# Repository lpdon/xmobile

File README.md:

# X-Mobile #

### What is this repository for? ###

Repository for the development of the version 2015 of the X-Mobile robot.

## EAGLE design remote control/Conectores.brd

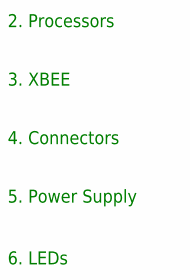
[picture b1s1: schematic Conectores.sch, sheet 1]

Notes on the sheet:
2. Processors
3. XBEE
4. Connectors
5. Power Supply
6. LEDs

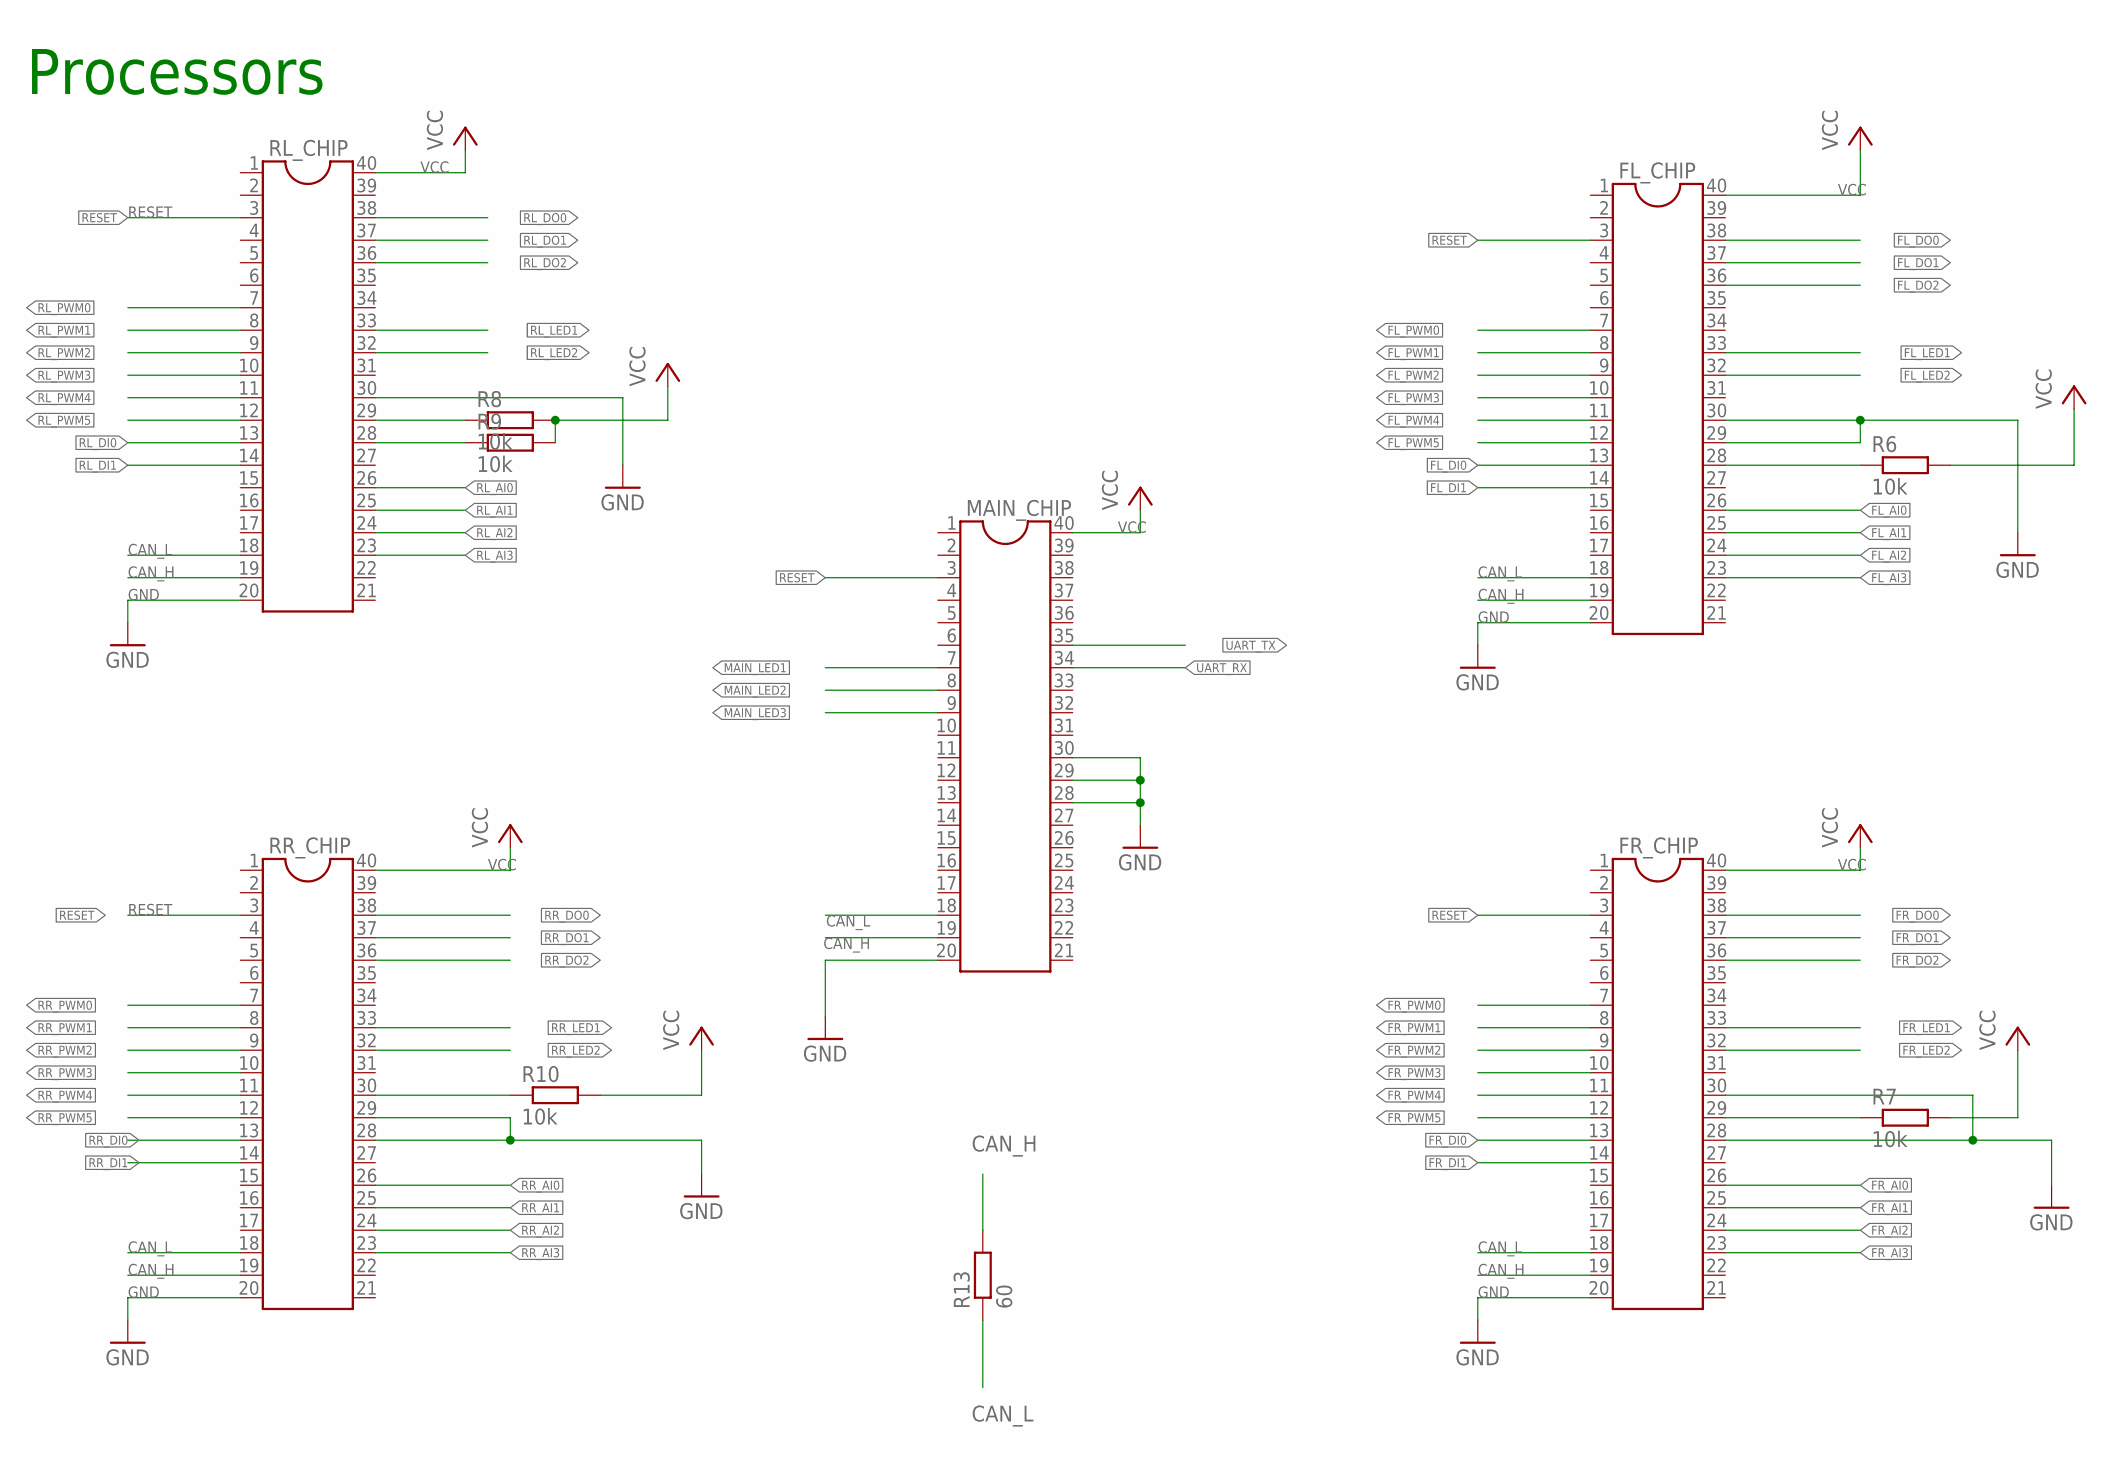
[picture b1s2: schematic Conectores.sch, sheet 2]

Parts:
FL_CHIP: DIL40
FR_CHIP: DIL40
MAIN_CHIP: DIL40
R6, R7, R8, R9, R10: 10k; M0805
R13: 60; R0805
RL_CHIP: DIL40
RR_CHIP: DIL40

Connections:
CAN_H: FL_CHIP.19, FR_CHIP.19, MAIN_CHIP.19, R13.2, RL_CHIP.19, RR_CHIP.19; also elsewhere on the board
CAN_L: FL_CHIP.18, FR_CHIP.18, MAIN_CHIP.18, R13.1, RL_CHIP.18, RR_CHIP.18; also elsewhere on the board
FL_AI0: FL_CHIP.26; also elsewhere on the board
FL_AI1: FL_CHIP.25; also elsewhere on the board
FL_AI2: FL_CHIP.24; also elsewhere on the board
FL_AI3: FL_CHIP.23; also elsewhere on the board
FL_DI0: FL_CHIP.13; also elsewhere on the board
FL_DI1: FL_CHIP.14; also elsewhere on the board
FL_DO0: FL_CHIP.38; also elsewhere on the board
FL_DO1: FL_CHIP.37; also elsewhere on the board
FL_DO2: FL_CHIP.36; also elsewhere on the board
FL_LED1: FL_CHIP.33; also elsewhere on the board
FL_LED2: FL_CHIP.32; also elsewhere on the board
FL_PWM0: FL_CHIP.7; also elsewhere on the board
FL_PWM1: FL_CHIP.8; also elsewhere on the board
FL_PWM2: FL_CHIP.9; also elsewhere on the board
FL_PWM3: FL_CHIP.10; also elsewhere on the board
FL_PWM4: FL_CHIP.11; also elsewhere on the board
FL_PWM5: FL_CHIP.12; also elsewhere on the board
FR_AI0: FR_CHIP.26; also elsewhere on the board
FR_AI1: FR_CHIP.25; also elsewhere on the board
FR_AI2: FR_CHIP.24; also elsewhere on the board
FR_AI3: FR_CHIP.23; also elsewhere on the board
FR_DI0: FR_CHIP.13; also elsewhere on the board
FR_DI1: FR_CHIP.14; also elsewhere on the board
FR_DIP2: FR_CHIP.29, R7.1
FR_DO0: FR_CHIP.38; also elsewhere on the board
FR_DO1: FR_CHIP.37; also elsewhere on the board
FR_DO2: FR_CHIP.36; also elsewhere on the board
FR_LED1: FR_CHIP.33; also elsewhere on the board
FR_LED2: FR_CHIP.32; also elsewhere on the board
FR_PWM0: FR_CHIP.7; also elsewhere on the board
FR_PWM1: FR_CHIP.8; also elsewhere on the board
FR_PWM2: FR_CHIP.9; also elsewhere on the board
FR_PWM3: FR_CHIP.10; also elsewhere on the board
FR_PWM4: FR_CHIP.11; also elsewhere on the board
FR_PWM5: FR_CHIP.12; also elsewhere on the board
GND: FL_CHIP.20, FL_CHIP.29, FL_CHIP.30, FR_CHIP.20, FR_CHIP.28, FR_CHIP.30, MAIN_CHIP.20, MAIN_CHIP.28, MAIN_CHIP.29, MAIN_CHIP.30, RL_CHIP.20, RL_CHIP.30, RR_CHIP.20, RR_CHIP.28, RR_CHIP.29; also elsewhere on the board
MAIN_LED1: MAIN_CHIP.7; also elsewhere on the board
MAIN_LED2: MAIN_CHIP.8; also elsewhere on the board
MAIN_LED3: MAIN_CHIP.9; also elsewhere on the board
unnamed: FL_CHIP.28, R6.1
RESET: FL_CHIP.3, FR_CHIP.3, MAIN_CHIP.3, RL_CHIP.3, RR_CHIP.3; also elsewhere on the board
RL_AI0: RL_CHIP.26; also elsewhere on the board
RL_AI1: RL_CHIP.25; also elsewhere on the board
RL_AI2: RL_CHIP.24; also elsewhere on the board
RL_AI3: RL_CHIP.23; also elsewhere on the board
RL_DI0: RL_CHIP.13; also elsewhere on the board
RL_DI1: RL_CHIP.14; also elsewhere on the board
RL_DIP2: R8.1, RL_CHIP.29
RL_DIP3: R9.1, RL_CHIP.28
RL_DO0: RL_CHIP.38; also elsewhere on the board
RL_DO1: RL_CHIP.37; also elsewhere on the board
RL_DO2: RL_CHIP.36; also elsewhere on the board
RL_LED1: RL_CHIP.33; also elsewhere on the board
RL_LED2: RL_CHIP.32; also elsewhere on the board
RL_PWM0: RL_CHIP.7; also elsewhere on the board
RL_PWM1: RL_CHIP.8; also elsewhere on the board
RL_PWM2: RL_CHIP.9; also elsewhere on the board
RL_PWM3: RL_CHIP.10; also elsewhere on the board
RL_PWM4: RL_CHIP.11; also elsewhere on the board
RL_PWM5: RL_CHIP.12; also elsewhere on the board
RR_AI0: RR_CHIP.26; also elsewhere on the board
RR_AI1: RR_CHIP.25; also elsewhere on the board
RR_AI2: RR_CHIP.24; also elsewhere on the board
RR_AI3: RR_CHIP.23; also elsewhere on the board
RR_DI0: RR_CHIP.13; also elsewhere on the board
RR_DI1: RR_CHIP.14; also elsewhere on the board
RR_DIP1: R10.1, RR_CHIP.30
RR_DO0: RR_CHIP.38; also elsewhere on the board
RR_DO1: RR_CHIP.37; also elsewhere on the board
RR_DO2: RR_CHIP.36; also elsewhere on the board
RR_LED1: RR_CHIP.33; also elsewhere on the board
RR_LED2: RR_CHIP.32; also elsewhere on the board
RR_PWM0: RR_CHIP.7; also elsewhere on the board
RR_PWM1: RR_CHIP.8; also elsewhere on the board
RR_PWM2: RR_CHIP.9; also elsewhere on the board
RR_PWM3: RR_CHIP.10; also elsewhere on the board
RR_PWM4: RR_CHIP.11; also elsewhere on the board
RR_PWM5: RR_CHIP.12; also elsewhere on the board
UART_RX: MAIN_CHIP.34; also elsewhere on the board
UART_TX: MAIN_CHIP.35; also elsewhere on the board
VCC: FL_CHIP.40, FR_CHIP.40, MAIN_CHIP.40, R6.2, R7.2, R8.2, R9.2, R10.2, RL_CHIP.40, RR_CHIP.40; also elsewhere on the board

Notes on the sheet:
Processors

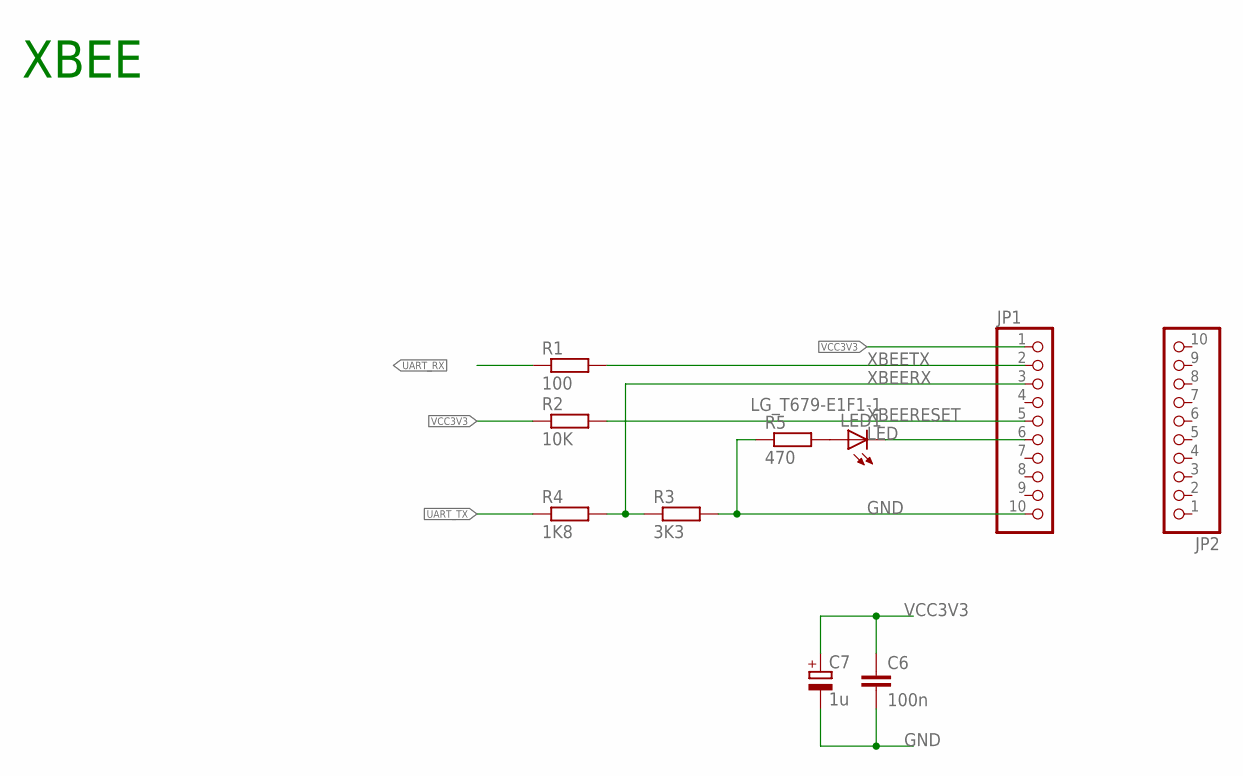
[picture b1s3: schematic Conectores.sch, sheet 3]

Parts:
C6: 100n; C0805
C7: 1u; CT3528
JP1, JP2: PINHD-1X10_2.00; 1X10M
LED1: LG_T679-E1F1-1; PLCC2
R1: 100; M0805
R2: 10K; M0805
R3: 3K3; M0805
R4: 1K8; M0805
R5: 470; M0805

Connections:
GND: C6.2, C7.-, JP1.10, R3.2, R5.1; also elsewhere on the board
LED: JP1.6, LED1.C
unnamed: LED1.A, R5.2
UART_RX: R1.1; also elsewhere on the board
UART_TX: R4.1; also elsewhere on the board
VCC3V3: C6.1, C7.+, JP1.1, R2.1; also elsewhere on the board
XBEERESET: JP1.5, R2.2
XBEERX: JP1.3, R3.1, R4.2
XBEETX: JP1.2, R1.2

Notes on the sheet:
XBEE

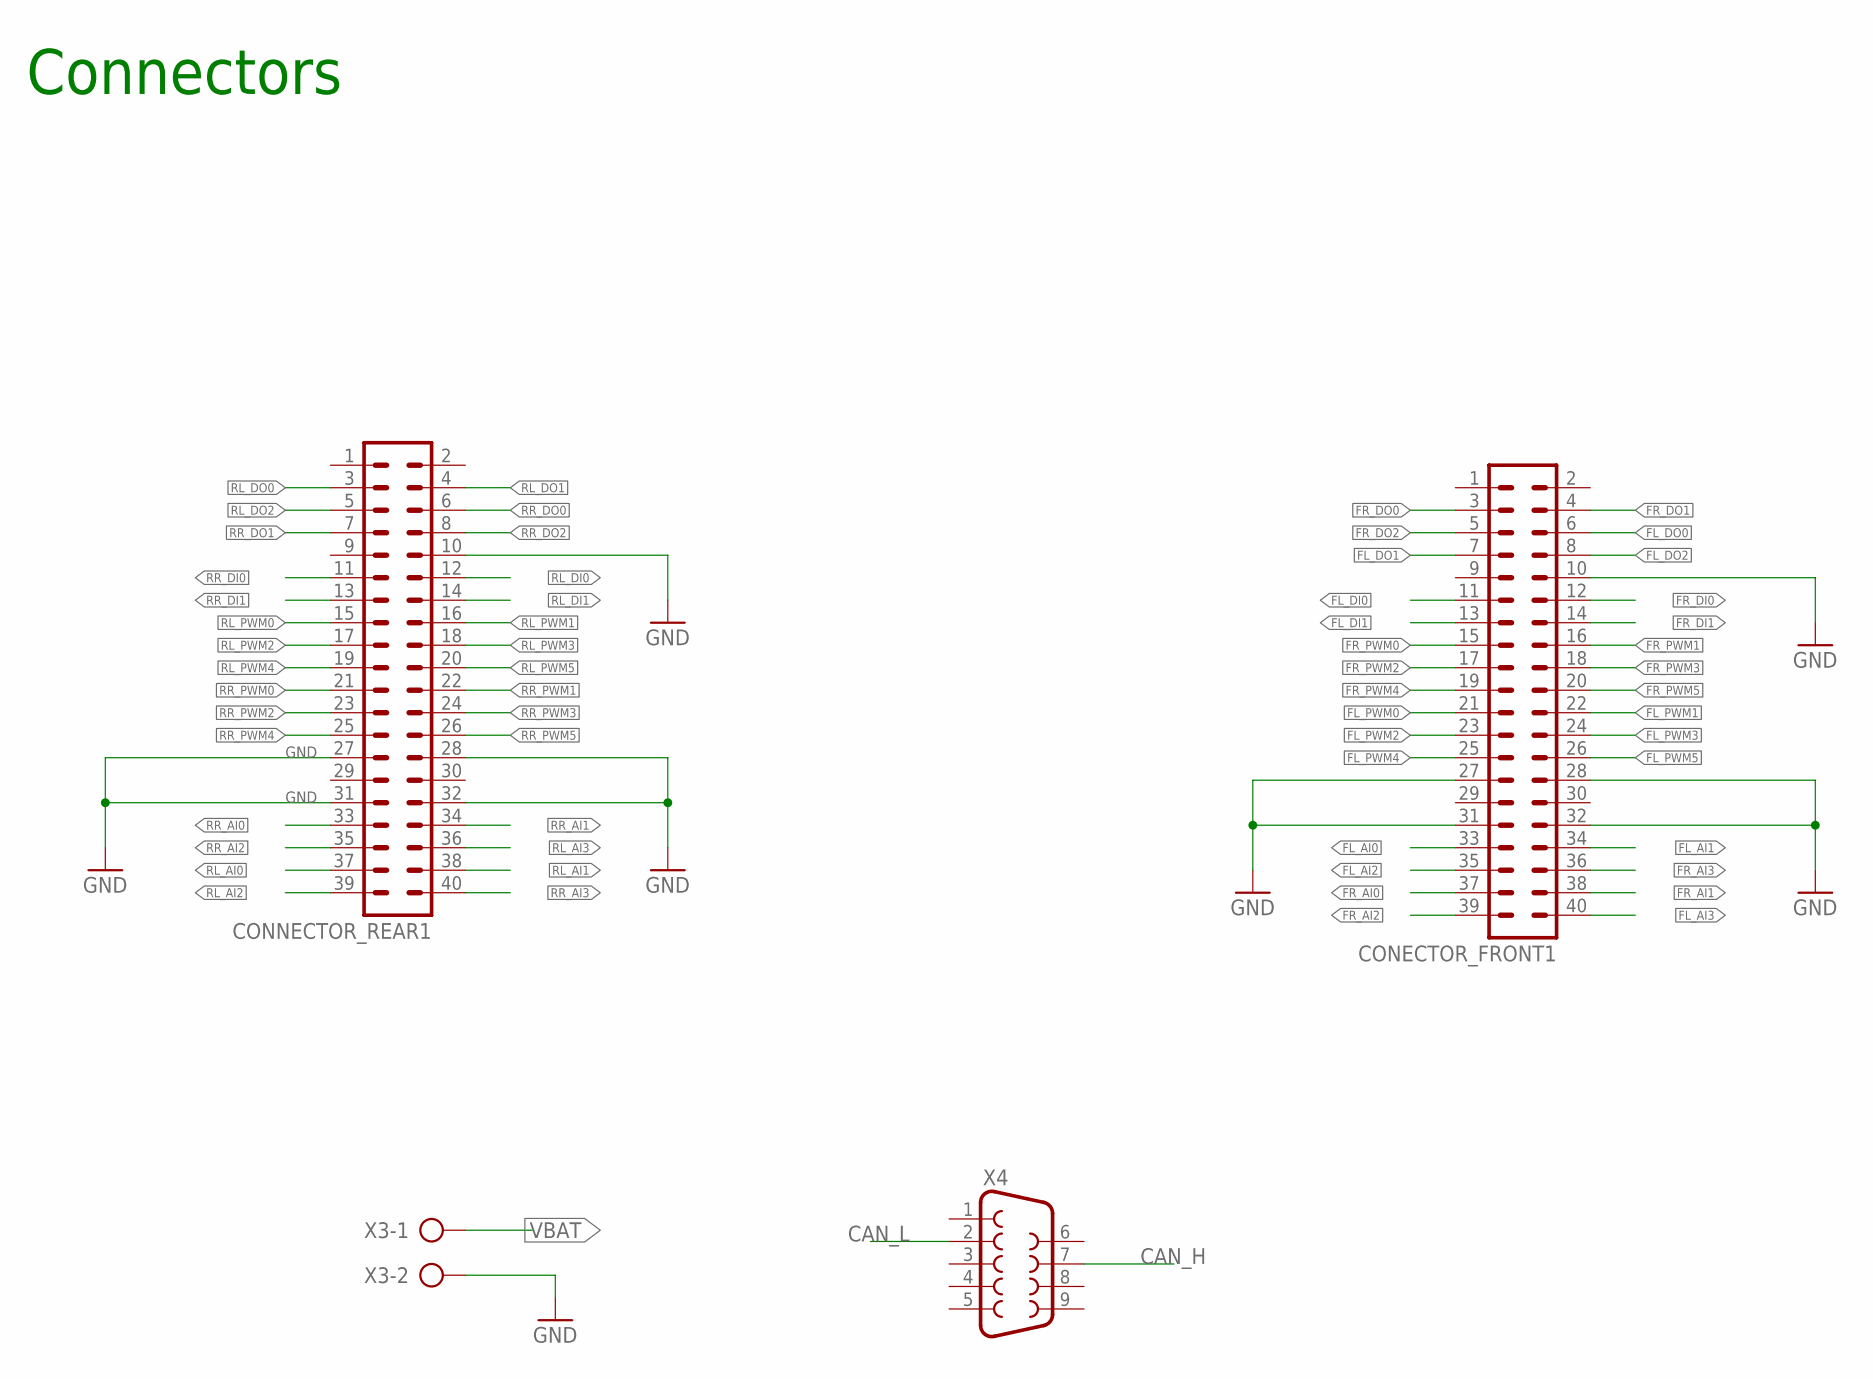
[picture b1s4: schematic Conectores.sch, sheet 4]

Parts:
CONECTOR_FRONT1: ML40
CONNECTOR_REAR1: ML40
X3: AK300/2
X4: F09HP

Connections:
CAN_H: X4.7; also elsewhere on the board
CAN_L: X4.2; also elsewhere on the board
FL_AI0: CONECTOR_FRONT1.33; also elsewhere on the board
FL_AI1: CONECTOR_FRONT1.34; also elsewhere on the board
FL_AI2: CONECTOR_FRONT1.35; also elsewhere on the board
FL_AI3: CONECTOR_FRONT1.40; also elsewhere on the board
FL_DI0: CONECTOR_FRONT1.11; also elsewhere on the board
FL_DI1: CONECTOR_FRONT1.13; also elsewhere on the board
FL_DO0: CONECTOR_FRONT1.6; also elsewhere on the board
FL_DO1: CONECTOR_FRONT1.7; also elsewhere on the board
FL_DO2: CONECTOR_FRONT1.8; also elsewhere on the board
FL_PWM0: CONECTOR_FRONT1.21; also elsewhere on the board
FL_PWM1: CONECTOR_FRONT1.22; also elsewhere on the board
FL_PWM2: CONECTOR_FRONT1.23; also elsewhere on the board
FL_PWM3: CONECTOR_FRONT1.24; also elsewhere on the board
FL_PWM4: CONECTOR_FRONT1.25; also elsewhere on the board
FL_PWM5: CONECTOR_FRONT1.26; also elsewhere on the board
FR_AI0: CONECTOR_FRONT1.37; also elsewhere on the board
FR_AI1: CONECTOR_FRONT1.38; also elsewhere on the board
FR_AI2: CONECTOR_FRONT1.39; also elsewhere on the board
FR_AI3: CONECTOR_FRONT1.36; also elsewhere on the board
FR_DI0: CONECTOR_FRONT1.12; also elsewhere on the board
FR_DI1: CONECTOR_FRONT1.14; also elsewhere on the board
FR_DO0: CONECTOR_FRONT1.3; also elsewhere on the board
FR_DO1: CONECTOR_FRONT1.4; also elsewhere on the board
FR_DO2: CONECTOR_FRONT1.5; also elsewhere on the board
FR_PWM0: CONECTOR_FRONT1.15; also elsewhere on the board
FR_PWM1: CONECTOR_FRONT1.16; also elsewhere on the board
FR_PWM2: CONECTOR_FRONT1.17; also elsewhere on the board
FR_PWM3: CONECTOR_FRONT1.18; also elsewhere on the board
FR_PWM4: CONECTOR_FRONT1.19; also elsewhere on the board
FR_PWM5: CONECTOR_FRONT1.20; also elsewhere on the board
GND: CONECTOR_FRONT1.10, CONECTOR_FRONT1.27, CONECTOR_FRONT1.28, CONECTOR_FRONT1.31, CONECTOR_FRONT1.32, CONNECTOR_REAR1.10, CONNECTOR_REAR1.27, CONNECTOR_REAR1.28, CONNECTOR_REAR1.31, CONNECTOR_REAR1.32, X3.2; also elsewhere on the board
RL_AI0: CONNECTOR_REAR1.37; also elsewhere on the board
RL_AI1: CONNECTOR_REAR1.38; also elsewhere on the board
RL_AI2: CONNECTOR_REAR1.39; also elsewhere on the board
RL_AI3: CONNECTOR_REAR1.36; also elsewhere on the board
RL_DI0: CONNECTOR_REAR1.12; also elsewhere on the board
RL_DI1: CONNECTOR_REAR1.14; also elsewhere on the board
RL_DO0: CONNECTOR_REAR1.3; also elsewhere on the board
RL_DO1: CONNECTOR_REAR1.4; also elsewhere on the board
RL_DO2: CONNECTOR_REAR1.5; also elsewhere on the board
RL_PWM0: CONNECTOR_REAR1.15; also elsewhere on the board
RL_PWM1: CONNECTOR_REAR1.16; also elsewhere on the board
RL_PWM2: CONNECTOR_REAR1.17; also elsewhere on the board
RL_PWM3: CONNECTOR_REAR1.18; also elsewhere on the board
RL_PWM4: CONNECTOR_REAR1.19; also elsewhere on the board
RL_PWM5: CONNECTOR_REAR1.20; also elsewhere on the board
RR_AI0: CONNECTOR_REAR1.33; also elsewhere on the board
RR_AI1: CONNECTOR_REAR1.34; also elsewhere on the board
RR_AI2: CONNECTOR_REAR1.35; also elsewhere on the board
RR_AI3: CONNECTOR_REAR1.40; also elsewhere on the board
RR_DI0: CONNECTOR_REAR1.11; also elsewhere on the board
RR_DI1: CONNECTOR_REAR1.13; also elsewhere on the board
RR_DO0: CONNECTOR_REAR1.6; also elsewhere on the board
RR_DO1: CONNECTOR_REAR1.7; also elsewhere on the board
RR_DO2: CONNECTOR_REAR1.8; also elsewhere on the board
RR_PWM0: CONNECTOR_REAR1.21; also elsewhere on the board
RR_PWM1: CONNECTOR_REAR1.22; also elsewhere on the board
RR_PWM2: CONNECTOR_REAR1.23; also elsewhere on the board
RR_PWM3: CONNECTOR_REAR1.24; also elsewhere on the board
RR_PWM4: CONNECTOR_REAR1.25; also elsewhere on the board
RR_PWM5: CONNECTOR_REAR1.26; also elsewhere on the board
VBAT: X3.1; also elsewhere on the board

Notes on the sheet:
Connectors

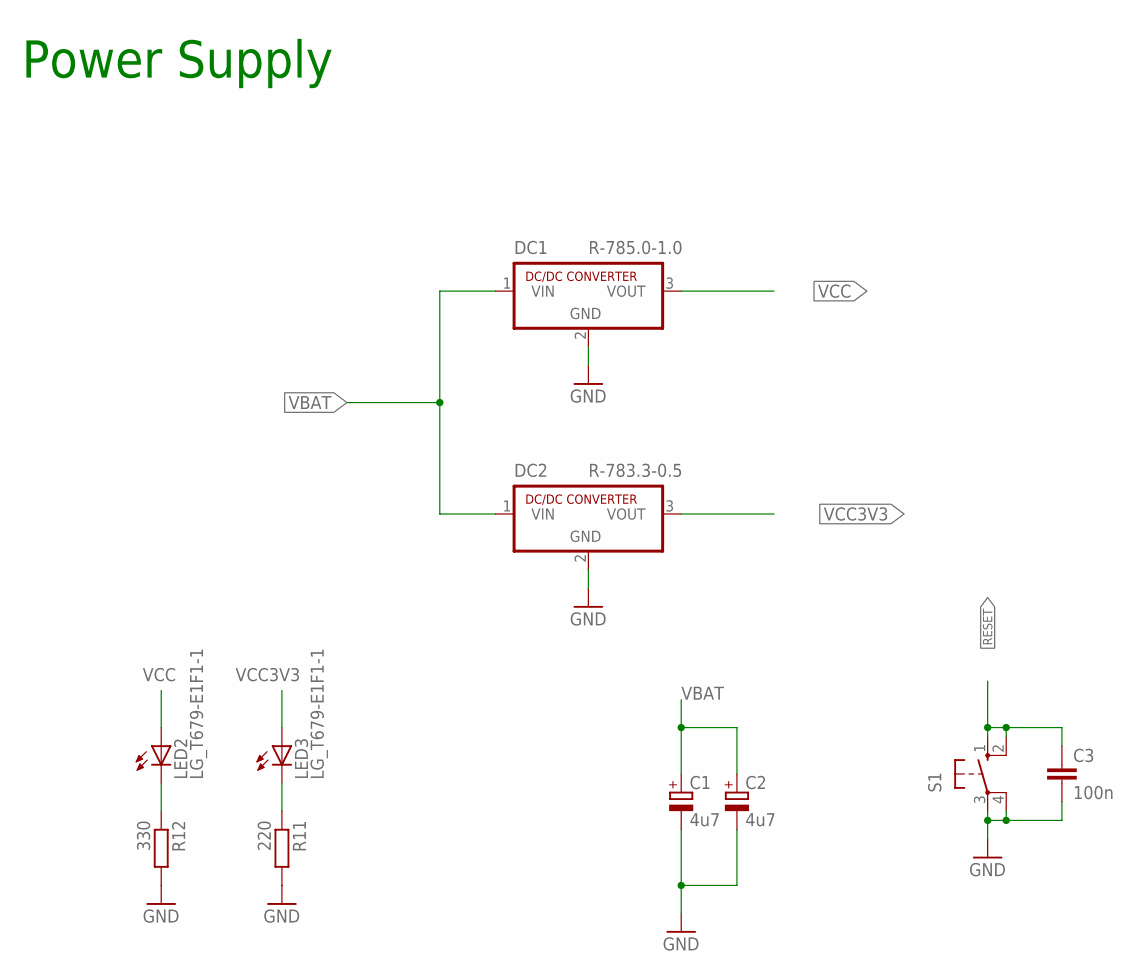
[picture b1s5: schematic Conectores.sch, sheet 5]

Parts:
C1, C2: 4u7; SMC_E
C3: 100n; C0805K
DC1: R-785.0-1.0; SIP3
DC2: R-783.3-0.5; SIP3
LED2, LED3: LG_T679-E1F1-1; PLCC2
R11: 220; R0805
R12: 330; R0805
S1: 10-XX; B3F-10XX

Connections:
GND: C1.-, C2.-, C3.2, DC1.2 (GND), DC2.2 (GND), R11.2, R12.2, S1.3, S1.4 (P1); also elsewhere on the board
unnamed: LED3.C, R11.1
unnamed: LED2.C, R12.1
RESET: C3.1, S1.1 (S), S1.2 (S1); also elsewhere on the board
VBAT: C1.+, C2.+, DC1.1 (VIN), DC2.1 (VIN); also elsewhere on the board
VCC: DC1.3 (VOUT), LED2.A; also elsewhere on the board
VCC3V3: DC2.3 (VOUT), LED3.A; also elsewhere on the board

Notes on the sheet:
Power Supply

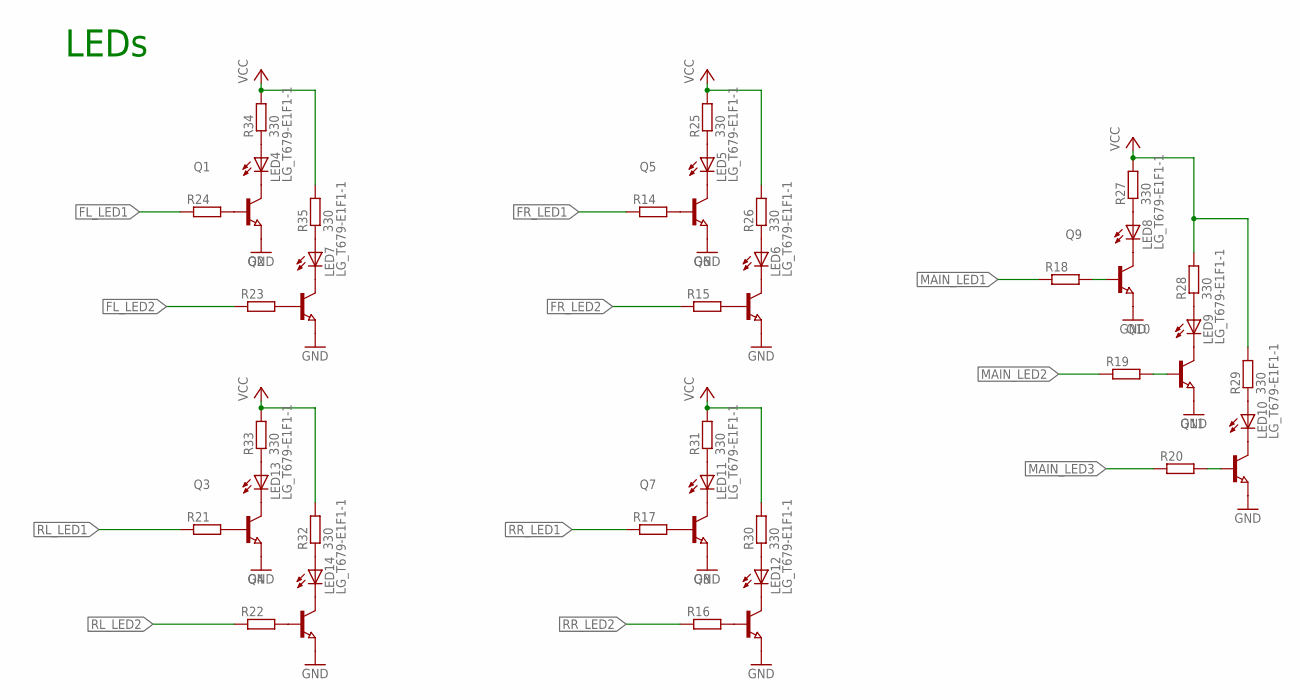
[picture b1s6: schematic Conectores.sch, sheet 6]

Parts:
LED4, LED5, LED6, LED7, LED8, LED9, LED10, LED11, LED12, LED13, LED14: LG_T679-E1F1-1; PLCC2
Q1, Q2, Q3, Q4, Q5, Q6, Q7, Q8, Q9, Q10, Q11: NPN-TRANSISTOR_SOT23; SOT23
R14, R15, R16, R17, R18, R19, R20, R21, R22, R23, R24: R-EU_R0805; R0805
R25, R26, R27, R28, R29, R30, R31, R32, R33, R34, R35: 330; R0805

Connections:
FL_LED1: R24.1; also elsewhere on the board
FL_LED2: R23.1; also elsewhere on the board
FR_LED1: R14.1; also elsewhere on the board
FR_LED2: R15.1; also elsewhere on the board
GND: Q1.2 (E), Q2.2 (E), Q3.2 (E), Q4.2 (E), Q5.2 (E), Q6.2 (E), Q7.2 (E), Q8.2 (E), Q9.2 (E), Q10.2 (E), Q11.2 (E); also elsewhere on the board
MAIN_LED1: R18.1; also elsewhere on the board
MAIN_LED2: R19.1; also elsewhere on the board
MAIN_LED3: R20.1; also elsewhere on the board
unnamed: Q5.1 (B), R14.2
unnamed: Q6.1 (B), R15.2
unnamed: Q8.1 (B), R16.2
unnamed: Q7.1 (B), R17.2
unnamed: Q3.1 (B), R21.2
unnamed: Q4.1 (B), R22.2
unnamed: Q1.1 (B), R24.2
unnamed: Q2.1 (B), R23.2
unnamed: LED4.C, Q1.3 (C)
unnamed: LED5.C, Q5.3 (C)
unnamed: LED8.C, Q9.3 (C)
unnamed: LED10.C, Q11.3 (C)
unnamed: LED11.C, Q7.3 (C)
unnamed: LED13.C, Q3.3 (C)
unnamed: LED7.C, Q2.3 (C)
unnamed: LED14.C, Q4.3 (C)
unnamed: LED6.C, Q6.3 (C)
unnamed: LED12.C, Q8.3 (C)
unnamed: LED9.C, Q10.3 (C)
unnamed: LED5.A, R25.1
unnamed: LED6.A, R26.1
unnamed: LED8.A, R27.1
unnamed: LED9.A, R28.1
unnamed: LED10.A, R29.1
unnamed: LED12.A, R30.1
unnamed: LED11.A, R31.1
unnamed: LED14.A, R32.1
unnamed: LED13.A, R33.1
unnamed: LED4.A, R34.1
unnamed: LED7.A, R35.1
unnamed: Q9.1 (B), R18.2
unnamed: Q10.1 (B), R19.2
unnamed: Q11.1 (B), R20.2
RL_LED1: R21.1; also elsewhere on the board
RL_LED2: R22.1; also elsewhere on the board
RR_LED1: R17.1; also elsewhere on the board
RR_LED2: R16.1; also elsewhere on the board
VCC: R25.2, R26.2, R27.2, R28.2, R29.2, R30.2, R31.2, R32.2, R33.2, R34.2, R35.2; also elsewhere on the board

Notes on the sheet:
LEDs

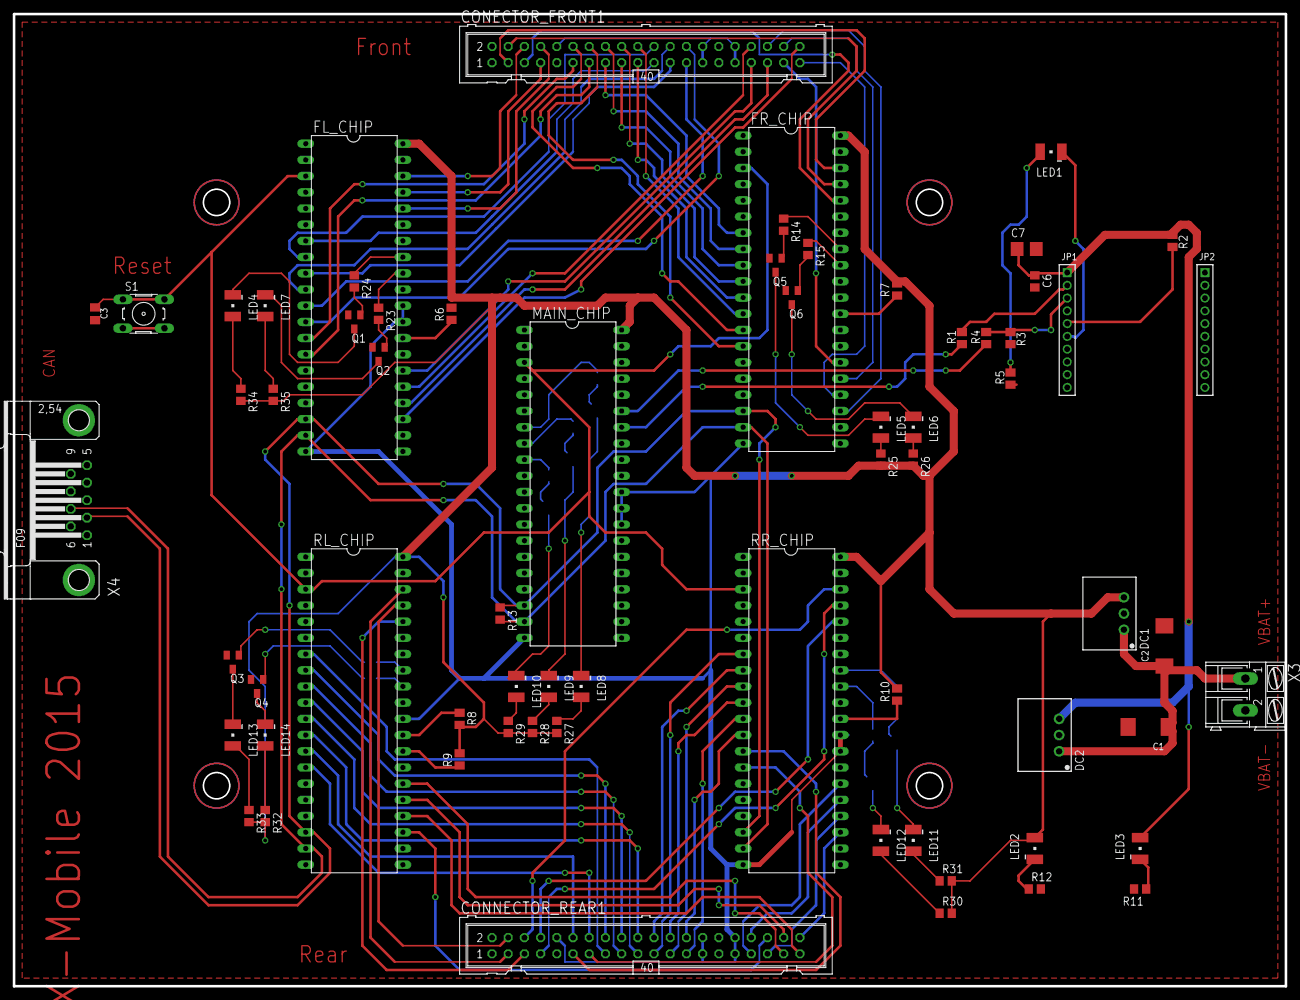
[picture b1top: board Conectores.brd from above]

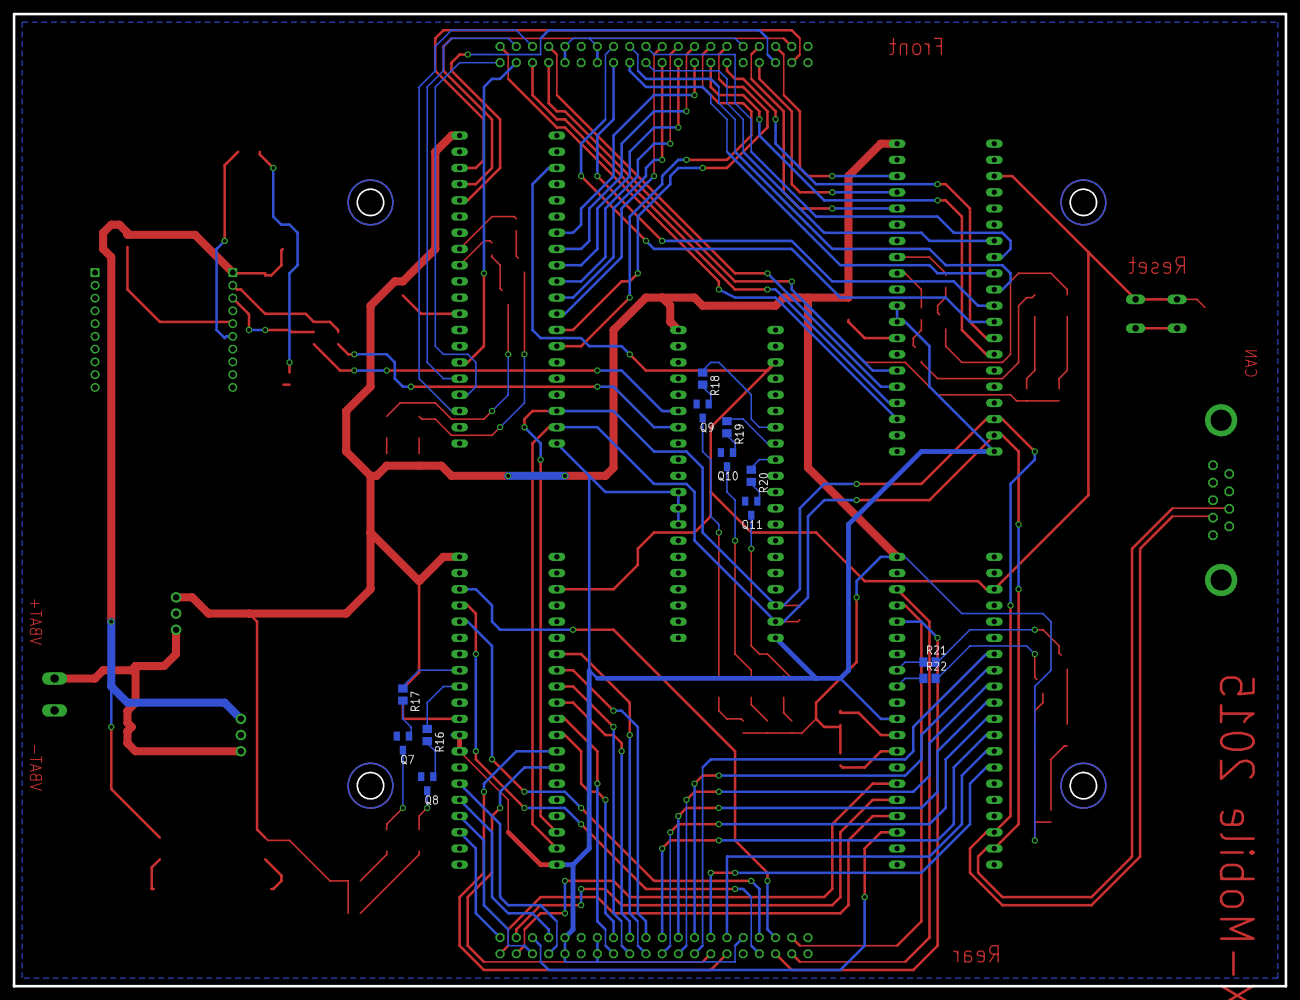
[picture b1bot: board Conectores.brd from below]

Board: 2 copper layers, 199.4 x 152.4 mm, 79 parts (12 on the bottom side), 125 nets.

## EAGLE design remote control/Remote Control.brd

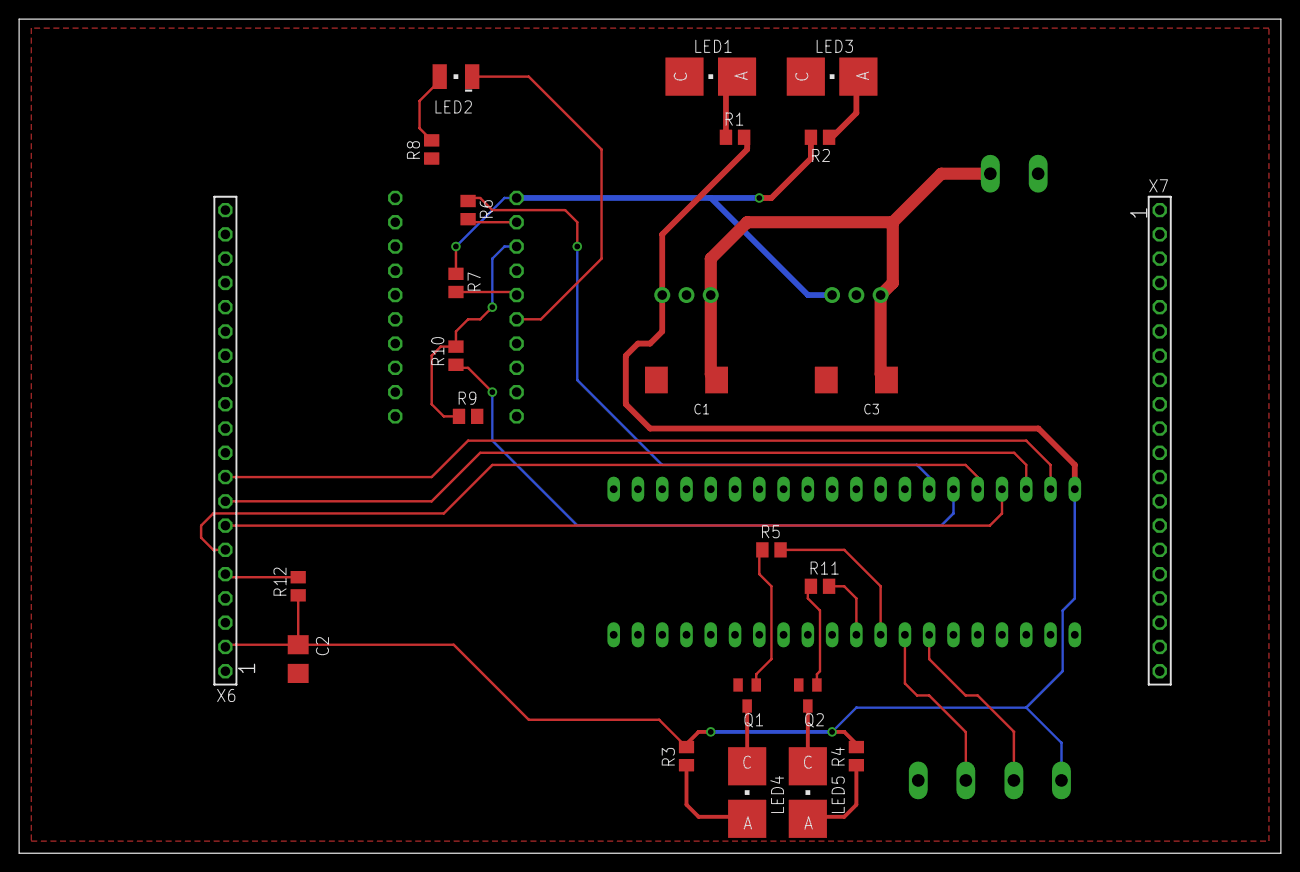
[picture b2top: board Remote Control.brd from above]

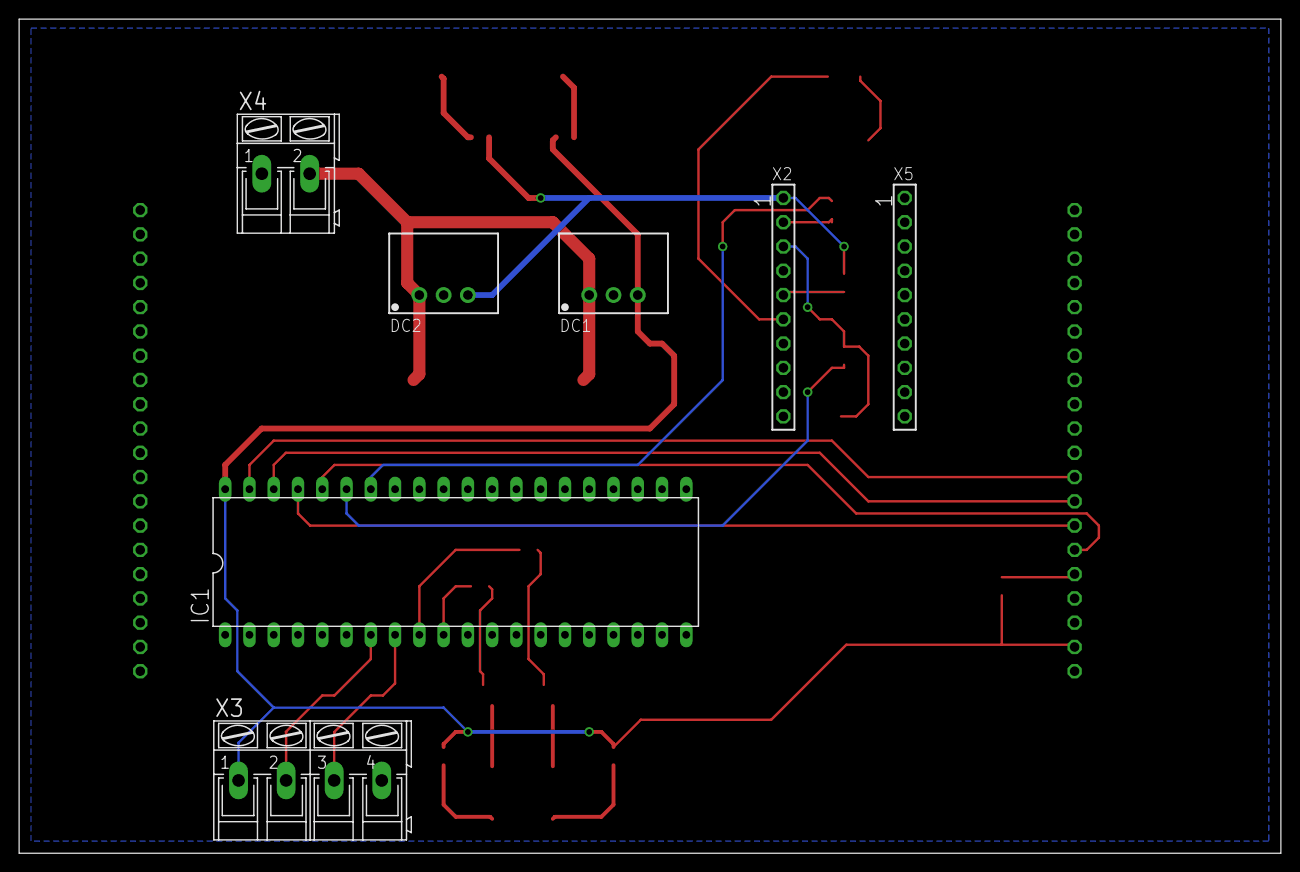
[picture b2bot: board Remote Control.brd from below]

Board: 2 copper layers, 132.1 x 87.3 mm, 31 parts (7 on the bottom side), 28 nets.

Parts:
C1, C3: 4u7; SMC_E
C2: 10u; CT3528
DC1: R-785.0-1.0; SIP3
DC2: R-783.3-0.5; SIP3
IC1: DIL40
LED1, LED3, LED4, LED5: P-LCC-2
LED2: LG_T679-E1F1-1; PLCC2
Q1, Q2: SOT23
R1, R3, R4: 330; M0805
R2: 220; M0805
R5, R11: 10k; M0805
R6: 100; M0805
R7, R12: 10K; M0805
R8: 470; M0805
R9: 3K3; M0805
R10: 1K8; M0805
X2, X5: SSW-110-02-S-S
X3: AK300/4
X4: AK300/2
X6, X7: SSW-120-02-S-S

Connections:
3V3: DC2.3, R2.2, R7.1, X2.1
5V: C2.+, DC1.3, IC1.40, R1.2, R3.2, R4.2, R12.1, X3.1, X6.2
GND: C1.-, C2.-, C3.-, DC1.2, DC2.2, IC1.20, LED1.C, LED3.C, Q1.2, Q2.2, R8.1, R9.2, X2.10, X3.4, X4.1, X6.1, X6.11
I2C_CLOCK: IC1.7, X3.2
I2C_DATA: IC1.8, X3.3
LED1: IC1.9, R5.2
LED2: IC1.10, R11.2
MISO: IC1.38, X6.8
MOSI: IC1.37, X6.7
unnamed: LED2.A, R8.2
unnamed: LED1.A, R1.1
unnamed: LED3.A, R2.1
unnamed: LED4.A, R3.1
unnamed: LED4.C, Q1.3
unnamed: LED5.A, R4.1
unnamed: LED5.C, Q2.3
unnamed: Q1.1, R5.1
unnamed: Q2.1, R11.1
unnamed: R12.2, X6.5
SCK: IC1.39, X6.9
SS: IC1.36, X6.6
UART_RX: IC1.34, R6.1
UART_TX: IC1.35, R10.1
VBAT: C1.+, C3.+, DC1.1, DC2.1, X4.2
XBEELED1: LED2.C, X2.6
XBEERESET1: R7.2, X2.5
XBEERX: R9.1, R10.2, X2.3
XBEETX: R6.2, X2.2

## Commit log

2015-06-13 Commit project codewarrior
2015-06-13 Added misc + cw license
2015-06-13 Added sw fifo
2015-06-14 Codewarrior Project builded for UART test purposes
2015-06-14 Update sw fifo
2015-06-14 Updates and UART for Windows tests
2015-06-15 Update communications
2015-06-16 Remote Control Schematics added
2015-06-16 Updated comm. Added support for triggered messages. Basic implementation finished, with some TODOs still missing. Code must still be tested
2015-06-16 README.md edited online with Bitbucket
2015-06-16 Added missing function to send triggered messages
2015-06-17 Remote Control almost final version
2015-06-18 Updated PID
2015-06-18 PID ADC Test added
2015-06-18 Updated comm e pid
2015-06-21 Updates comm/crc/pid
2015-06-26 Updates communication
2015-06-28 Update comm
2015-06-28 Working handshake
2015-07-03 pre bus_interface
2015-07-03 Updated libs
2015-07-04 Max error added to pid
2015-07-04 Working communication with bus interface
2015-07-05 test pwm over xbee
2015-07-05 Test CAN
2015-07-05 Bugfix can
2015-07-06 Updated comm and bugfixes
2015-07-10 New libs + bugfixes
2015-07-12 Boards and bugfixes
2015-07-12 Updates and bugfixes
2015-07-14 First time nunchuk control :)
2015-07-20 First working version
2015-07-22 PID 32 bits and Drive 16 bits
2015-07-23 Opmode added, update comm, bugfixes
2015-08-09 Version presented on Familientag 2015
2015-08-23 Version presented on ZF Familientag
